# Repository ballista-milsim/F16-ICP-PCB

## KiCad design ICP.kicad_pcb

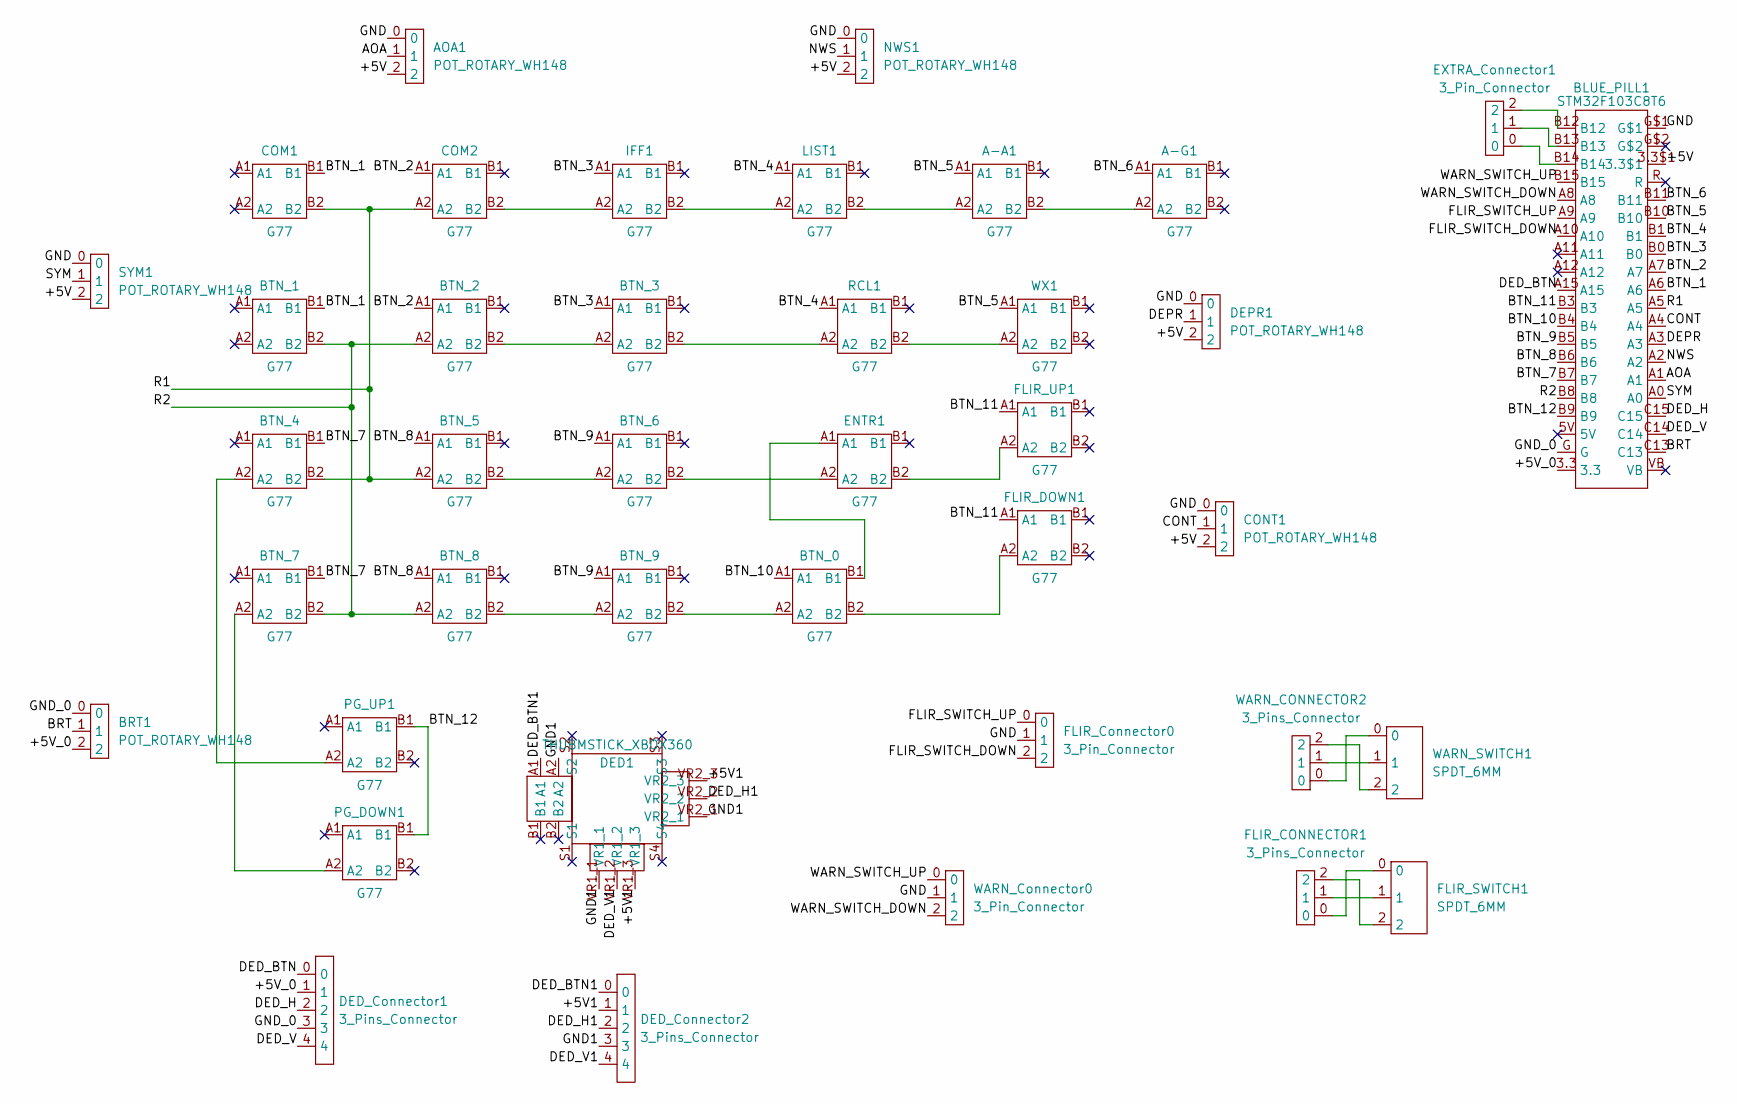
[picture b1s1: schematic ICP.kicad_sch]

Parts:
A-A1: G77; PUSH_BUTTON_G77
A-G1: G77; PUSH_BUTTON_G77
AOA1: POT_ROTARY_WH148; 3_PIN_CONNECTOR
BLUE_PILL1: STM32F103C8T6; STM32F103C8T6_BLUE_PILL
BRT1: POT_ROTARY_WH148; 3_PIN_CONNECTOR
BTN_0, BTN_1, BTN_2, BTN_3, BTN_4, BTN_5, BTN_6, BTN_7, BTN_8, BTN_9: G77; PUSH_BUTTON_G77
COM1, COM2: G77; PUSH_BUTTON_G77
CONT1: POT_ROTARY_WH148; 3_PIN_CONNECTOR
DED1: THUBMSTICK_XBOX360; THUMBSTICK_XBOX360
DED_Connector1, DED_Connector2: 3_Pins_Connector; 5_PIN_CONNECTOR
DEPR1: POT_ROTARY_WH148; 3_PIN_CONNECTOR
ENTR1: G77; PUSH_BUTTON_G77
EXTRA_Connector1: 3_Pin_Connector; 3_PIN_CONNECTOR
FLIR_CONNECTOR1: 3_Pins_Connector; 3_PIN_CONNECTOR
FLIR_Connector0: 3_Pin_Connector; 3_PIN_CONNECTOR
FLIR_DOWN1: G77; PUSH_BUTTON_G77
FLIR_SWITCH1: SPDT_6MM; TOGGLE_SWITCH_SPDT_6MM
FLIR_UP1: G77; PUSH_BUTTON_G77
IFF1: G77; PUSH_BUTTON_G77
LIST1: G77; PUSH_BUTTON_G77
NWS1: POT_ROTARY_WH148; 3_PIN_CONNECTOR
PG_DOWN1: G77; PUSH_BUTTON_G77
PG_UP1: G77; PUSH_BUTTON_G77
RCL1: G77; PUSH_BUTTON_G77
SYM1: POT_ROTARY_WH148; 3_PIN_CONNECTOR
WARN_CONNECTOR2: 3_Pins_Connector; 3_PIN_CONNECTOR
WARN_Connector0: 3_Pin_Connector; 3_PIN_CONNECTOR
WARN_SWITCH1: SPDT_6MM; TOGGLE_SWITCH_SPDT_6MM
WX1: G77; PUSH_BUTTON_G77

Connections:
/+5V: AOA1.2, BLUE_PILL1.3.3$1, CONT1.2, DEPR1.2, NWS1.2, SYM1.2
/+5V1: DED1.VR1_3, DED1.VR2_3, DED_Connector2.1
/+5V_0: BLUE_PILL1.3.3, BRT1.2, DED_Connector1.1
/AOA: AOA1.1, BLUE_PILL1.A1
/BRT: BLUE_PILL1.C13, BRT1.1
/BTN_1: BLUE_PILL1.A6, BTN_1.B1, COM1.B1
/BTN_2: BLUE_PILL1.A7, BTN_2.A1, COM2.A1
/BTN_3: BLUE_PILL1.B0, BTN_3.A1, IFF1.A1
/BTN_4: BLUE_PILL1.B1, LIST1.A1, RCL1.A1
/BTN_5: A-A1.A1, BLUE_PILL1.B10, WX1.A1
/BTN_6: A-G1.A1, BLUE_PILL1.B11
/BTN_7: BLUE_PILL1.B7, BTN_4.B1, BTN_7.B1
/BTN_8: BLUE_PILL1.B6, BTN_5.A1, BTN_8.A1
/BTN_9: BLUE_PILL1.B5, BTN_6.A1, BTN_9.A1
/BTN_10: BLUE_PILL1.B4, BTN_0.A1
/BTN_11: BLUE_PILL1.B3, FLIR_DOWN1.A1, FLIR_UP1.A1
/BTN_12: BLUE_PILL1.B9, PG_DOWN1.B1, PG_UP1.B1
/CONT: BLUE_PILL1.A4, CONT1.1
/DED_BTN: BLUE_PILL1.A15, DED_Connector1.0
/DED_BTN1: DED1.A1, DED_Connector2.0
/DED_H: BLUE_PILL1.C15, DED_Connector1.2
/DED_H1: DED1.VR2_2, DED_Connector2.2
/DED_V: BLUE_PILL1.C14, DED_Connector1.4
/DED_V1: DED1.VR1_2, DED_Connector2.4
/DEPR: BLUE_PILL1.A3, DEPR1.1
/FLIR_SWITCH_DOWN: BLUE_PILL1.A10, FLIR_Connector0.2
/FLIR_SWITCH_UP: BLUE_PILL1.A9, FLIR_Connector0.0
/GND: AOA1.0, BLUE_PILL1.G$1, CONT1.0, DEPR1.0, FLIR_Connector0.1, NWS1.0, SYM1.0, WARN_Connector0.1
/GND1: DED1.A2, DED1.VR1_1, DED1.VR2_1, DED_Connector2.3
/GND_0: BLUE_PILL1.G, BRT1.0, DED_Connector1.3
/NWS: BLUE_PILL1.A2, NWS1.1
/R1: BLUE_PILL1.A5, BTN_4.B2, BTN_5.A2, COM1.B2, COM2.A2
/R2: BLUE_PILL1.B8, BTN_1.B2, BTN_2.A2, BTN_7.B2, BTN_8.A2
/SYM: BLUE_PILL1.A0, SYM1.1
/WARN_SWITCH_DOWN: BLUE_PILL1.A8, WARN_Connector0.2
/WARN_SWITCH_UP: BLUE_PILL1.B15, WARN_Connector0.0
unnamed: A-A1.A2, LIST1.B2
unnamed: A-A1.B2, A-G1.A2
unnamed: BLUE_PILL1.B12, EXTRA_Connector1.2
unnamed: BLUE_PILL1.B13, EXTRA_Connector1.1
unnamed: BLUE_PILL1.B14, EXTRA_Connector1.0
unnamed: BTN_0.A2, BTN_9.B2
unnamed: BTN_0.B1, ENTR1.A1
unnamed: BTN_0.B2, FLIR_DOWN1.A2
unnamed: BTN_2.B2, BTN_3.A2
unnamed: BTN_3.B2, RCL1.A2
unnamed: BTN_4.A2, PG_UP1.A2
unnamed: BTN_5.B2, BTN_6.A2
unnamed: BTN_6.B2, ENTR1.A2
unnamed: BTN_7.A2, PG_DOWN1.A2
unnamed: BTN_8.B2, BTN_9.A2
unnamed: COM2.B2, IFF1.A2
unnamed: ENTR1.B2, FLIR_UP1.A2
unnamed: FLIR_CONNECTOR1.0, FLIR_SWITCH1.0
unnamed: FLIR_CONNECTOR1.1, FLIR_SWITCH1.1
unnamed: FLIR_CONNECTOR1.2, FLIR_SWITCH1.2
unnamed: IFF1.B2, LIST1.A2
unnamed: RCL1.B2, WX1.A2
unnamed: WARN_CONNECTOR2.0, WARN_SWITCH1.0
unnamed: WARN_CONNECTOR2.1, WARN_SWITCH1.1
unnamed: WARN_CONNECTOR2.2, WARN_SWITCH1.2

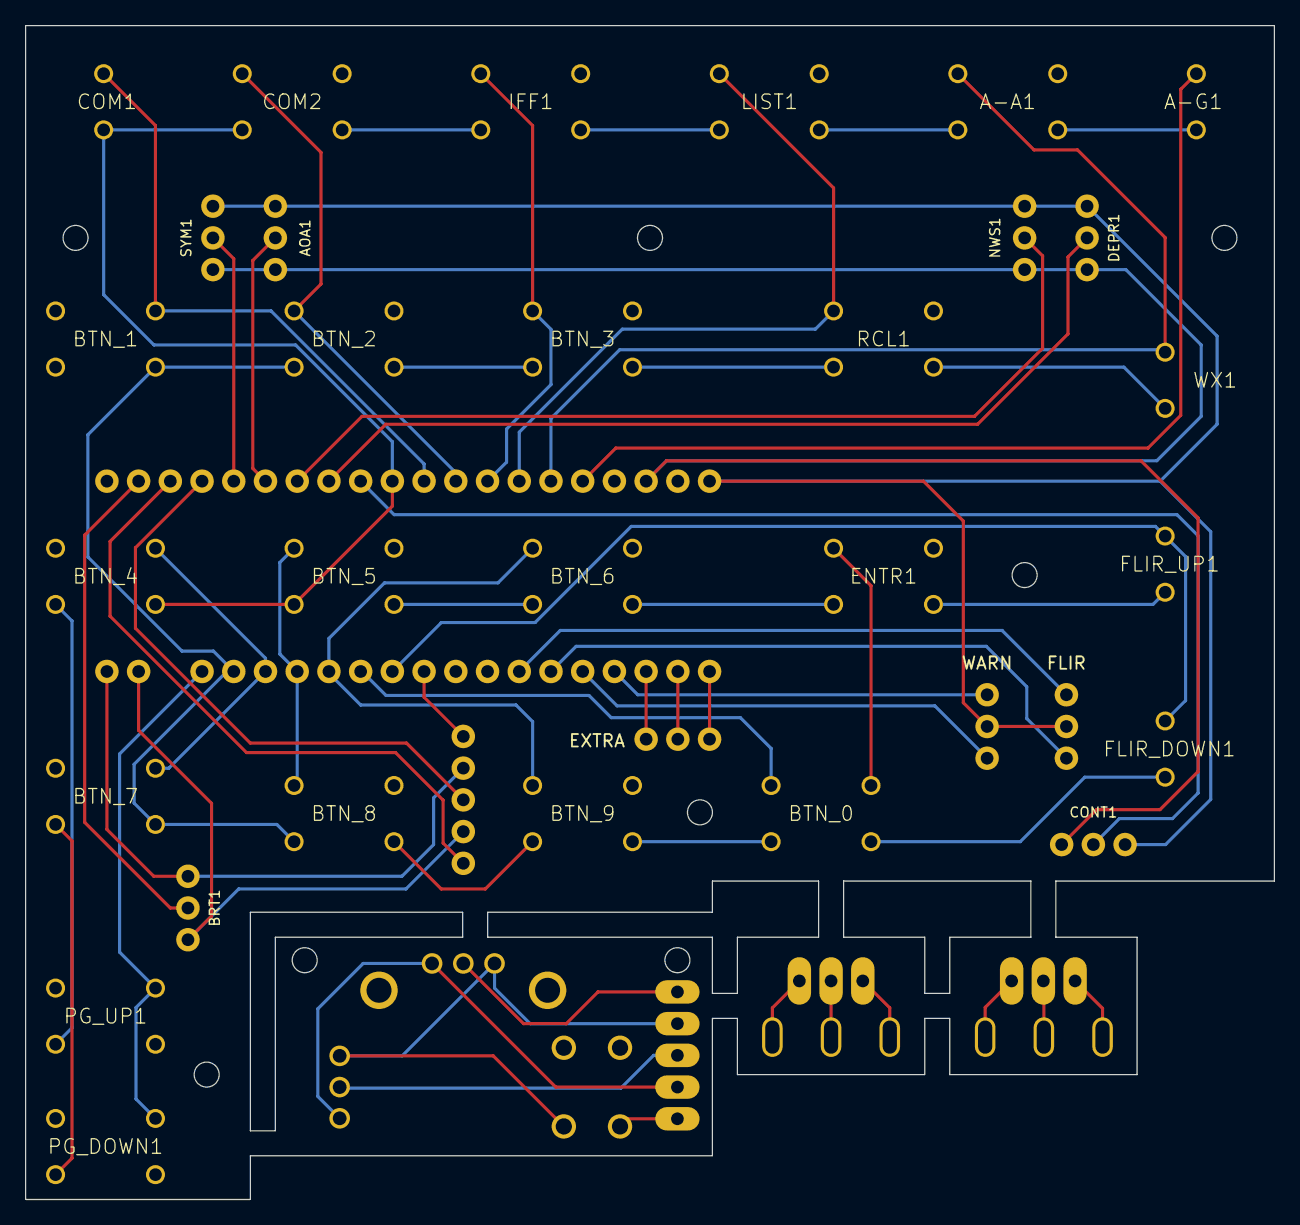
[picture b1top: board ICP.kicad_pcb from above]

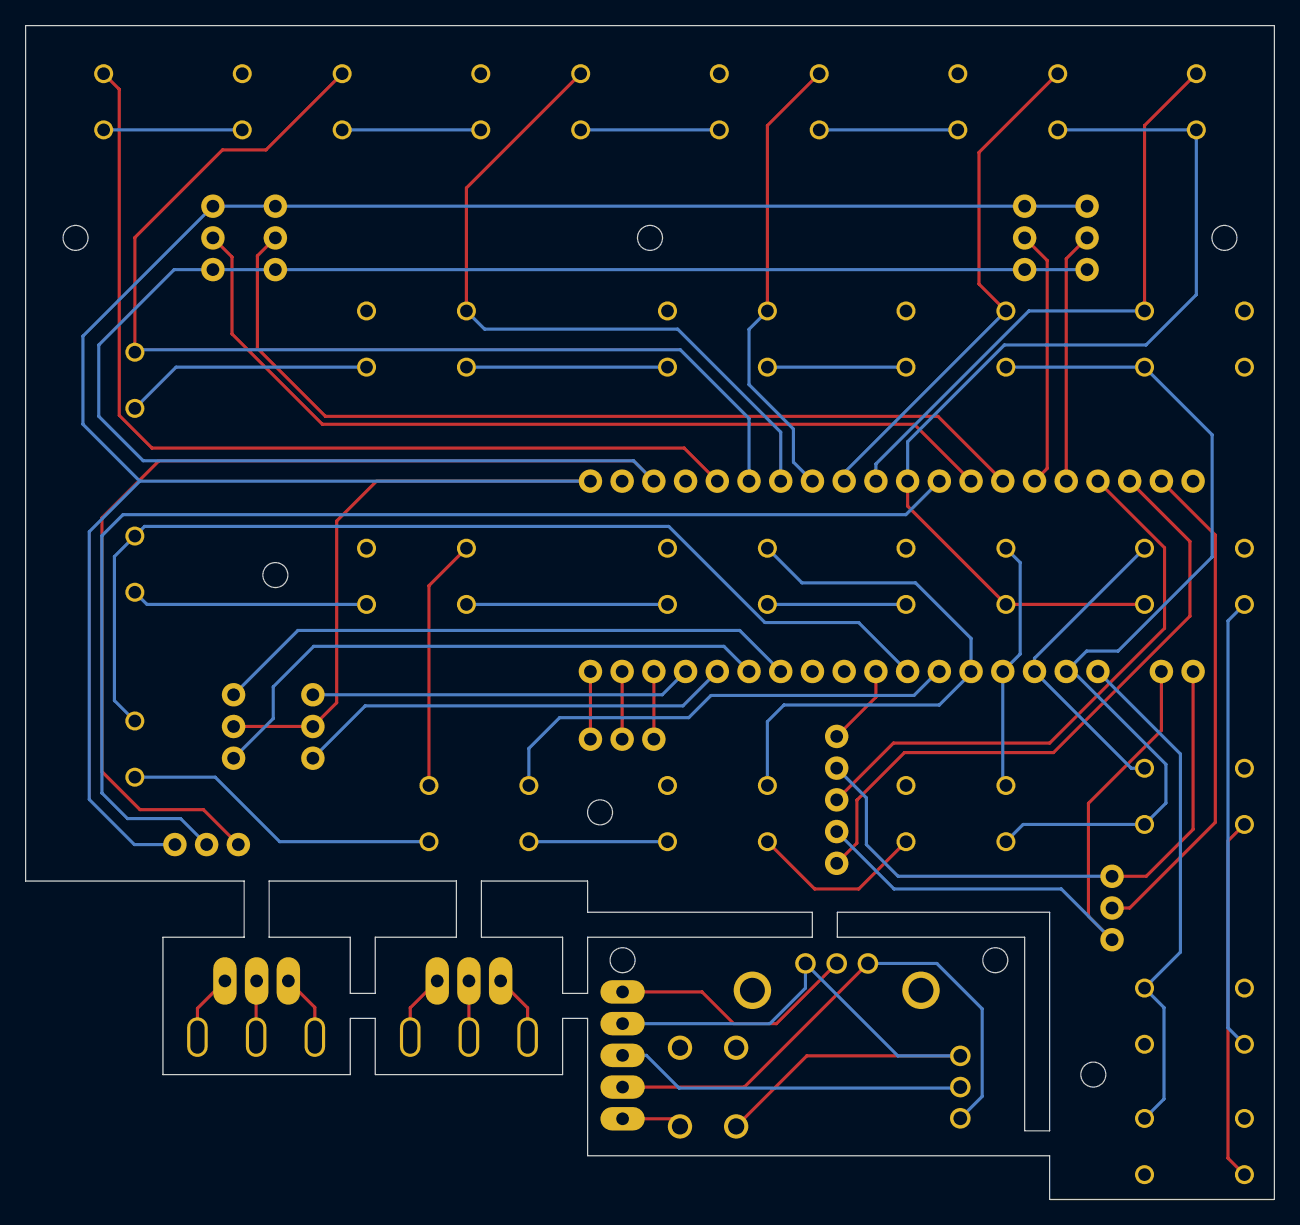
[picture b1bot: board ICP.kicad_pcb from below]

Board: 2 copper layers, 100.0 x 94.0 mm, 40 parts (11 on the bottom side), 61 nets.
